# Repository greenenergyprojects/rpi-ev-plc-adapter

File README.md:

# rpi-ev-plc-adapter

Electrovehicle CP/PLC Adapter for Raspberry PI

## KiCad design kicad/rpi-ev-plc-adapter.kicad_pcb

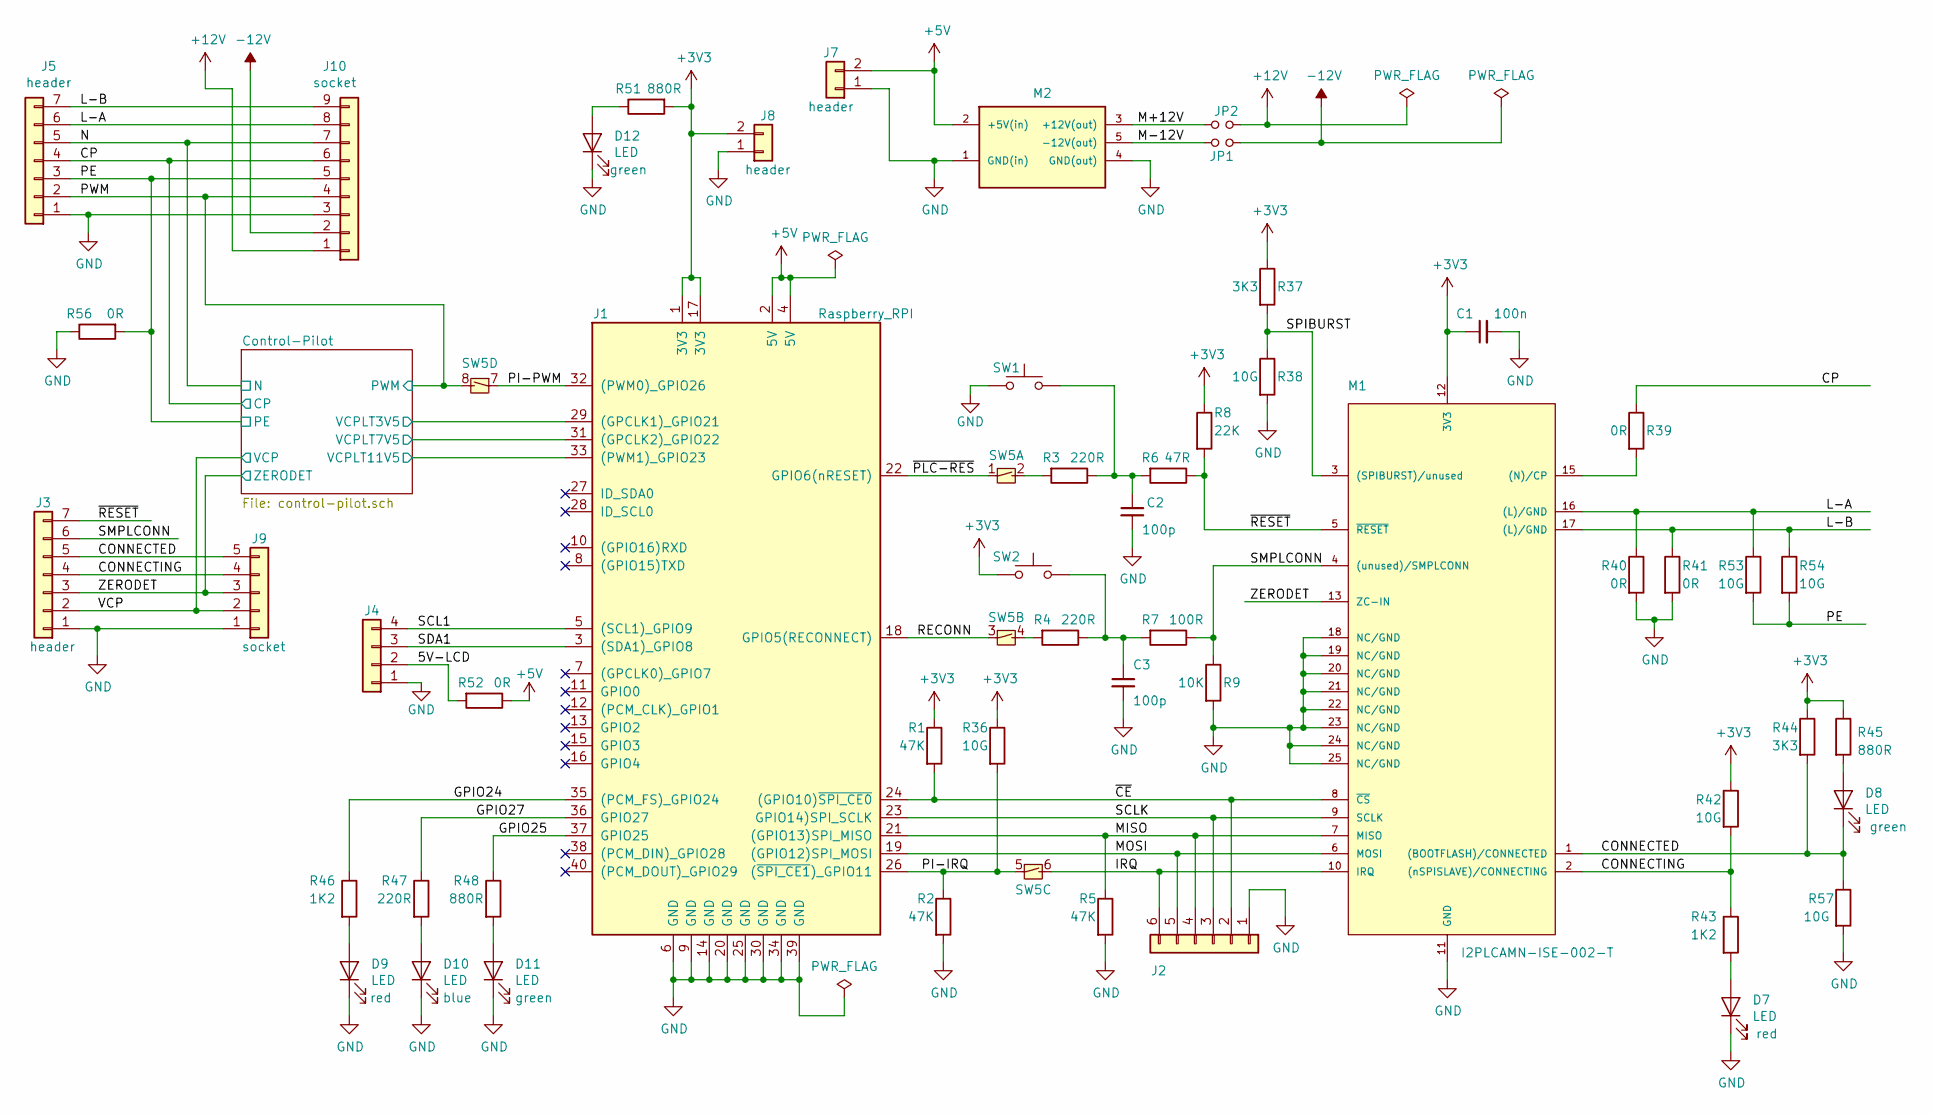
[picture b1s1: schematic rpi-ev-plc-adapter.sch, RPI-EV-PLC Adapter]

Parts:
C1: 100n; c-1206-hand-soldering
C2, C3: 100p; c-1206-hand-soldering
D7, D8, D9, D10, D11, D12: LED; LED_0805_HandSoldering
J1: Raspberry_RPI; Raspberry-PI
J2: Conn_01x06; idc-header-1x06-p2.54mm-vertical
J3, J5: header; idc-header-1x07-p2.54mm-vertical
J4: header; idc-header-1x04-p2.54mm-vertical
J7, J8: header; idc-header-1x02-p2.54mm-vertical
J9: socket; idc-socket-vertical-2.54mm_1x05
J10: socket; idc-socket-1x09-p2.54mm-vertical
JP1, JP2: Jumper_NO_Small; idc-header-1x02-p2.54mm-vertical
M1: I2PLCAMN-ISE-002-T
M2: supply-5VtoPM12V_ebay-253052736386; 5V-to-PM12V_ebay-253052736386
R1, R2, R5: 47K; r-1206-hand-soldering
R3, R4, R47: 220R; r-1206-hand-soldering
R6: 47R; r-1206-hand-soldering
R7: 100R; r-1206-hand-soldering
R8: 22K; r-1206-hand-soldering
R9: 10K; r-1206-hand-soldering
R36, R38, R42, R53, R54, R57: 10G; r-0805-hand-soldering
R37, R44: 3K3; r-1206-hand-soldering
R39, R40, R41, R52, R56: 0R; r-1206-hand-soldering
R43, R46: 1K2; r-1206-hand-soldering
R45, R51: 880R; r-1206-hand-soldering
R48: 880R; r-0805-hand-soldering
SW1, SW2: push-button_ebay-183284526496; push-button-smd-4.5x4.5mm-black
SW5: dip-switch-4x2pos-smd-1.27mm

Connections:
+3V3: C1.1, J1.1 (3V3), J1.17 (3V3), J8.2, M1.12 (3V3), R1.1, R8.1, R36.1, R37.1, R42.1, R44.1, R45.1, R51.2, SW2.1; also elsewhere on the board
+5V: J1.2 (5V), J1.4 (5V), J7.2, M2.2 (+5V(in)), R52.1
+12V: J10.1, JP2.2; also elsewhere on the board
-12V: J10.2, JP1.2; also elsewhere on the board
/5V-LCD: J4.2, R52.2
/CONNECTED: D8.1 (K), J3.5, J9.5, M1.1 ((BOOTFLASH)/CONNECTED), R44.2, R57.1
/CONNECTING: J3.4, J9.4, M1.2 ((nSPISLAVE)/CONNECTING), R42.2, R43.1
/CP: J5.4, J10.6, R39.1; also elsewhere on the board
/Control-Pilot/VCPLT3V5: J1.29 ((GPCLK1)_GPIO21); also elsewhere on the board
/Control-Pilot/VCPLT7V5: J1.31 ((GPCLK2)_GPIO22); also elsewhere on the board
/Control-Pilot/VCPLT11V5: J1.33 ((PWM1)_GPIO23); also elsewhere on the board
/GPIO24: J1.35 ((PCM_FS)_GPIO24), R46.1
/GPIO25: J1.37 (GPIO25), R48.1
/GPIO27: J1.36 (GPIO27), R47.1
/IRQ: J2.6, M1.10 (IRQ), SW5.6 (4)
/L-A: J5.6, J10.8, M1.16 ((L)/GND), R40.1, R53.1
/L-B: J5.7, J10.9, M1.17 ((L)/GND), R41.1, R54.1
/M+12V: JP2.1, M2.3 (+12V(out))
/M-12V: JP1.1, M2.5 (-12V(out))
/MISO: J1.21 ((GPIO13)SPI_MISO), J2.4, M1.7 (MISO), R5.1
/MOSI: J1.19 ((GPIO12)SPI_MOSI), J2.5, M1.6 (MOSI)
/N: J5.5, J10.7; also elsewhere on the board
/PE: J5.3, J10.5, R53.2, R54.2, R56.2; also elsewhere on the board
/PI-IRQ: J1.26 ((~SPI_CE1~)_GPIO11), R2.1, R36.2, SW5.5 (3)
/PI-PWM: J1.32 ((PWM0)_GPIO26), SW5.7 (3)
/PWM: J5.2, J10.4, SW5.8 (4); also elsewhere on the board
/RECONN: J1.18 (GPIO5(RECONNECT)), SW5.3
/SCL1: J1.5 ((SCL1)_GPIO9), J4.4
/SCLK: J1.23 (GPIO14)SPI_SCLK), J2.3, M1.9 (SCLK)
/SDA1: J1.3 ((SDA1)_GPIO8), J4.3
/SMPLCONN: J3.6, M1.4 ((unused)/SMPLCONN), R7.1, R9.1
/SPIBURST: M1.3 ((SPIBURST)/unused), R37.2, R38.1
/VCP: J3.2, J9.2; also elsewhere on the board
/ZERODET: J3.3, J9.3, M1.13 (ZC-IN); also elsewhere on the board
/~CE: J1.24 ((GPIO10)~SPI_CE0~), J2.2, M1.8 (~CS), R1.2
/~PLC-RES: J1.22 (GPIO6(nRESET)), SW5.1
/~RESET: J3.7, M1.5 (~RESET), R6.1, R8.2
GND: C1.2, C2.2, C3.2, D7.1 (K), D9.1 (K), D10.1 (K), D11.1 (K), D12.1 (K), J1.6 (GND), J1.9 (GND), J1.14 (GND), J1.20 (GND), J1.25 (GND), J1.30 (GND), J1.34 (GND), J1.39 (GND), J2.1, J3.1, J4.1, J5.1, J7.1, J8.1, J9.1, J10.3, M1.11 (GND), M1.18 (NC/GND), M1.19 (NC/GND), M1.20 (NC/GND), M1.21 (NC/GND), M1.22 (NC/GND), M1.23 (NC/GND), M1.24 (NC/GND), M1.25 (NC/GND), M2.1 (GND(in)), M2.4 (GND(out)), R2.2, R5.2, R9.2, R38.2, R40.2, R41.2, R56.1, R57.2, SW1.1; also elsewhere on the board
unnamed: C2.1, R3.1, R6.2, SW1.2
unnamed: C3.1, R4.1, R7.2, SW2.2
unnamed: D7.2 (A), R43.2
unnamed: D8.2 (A), R45.2
unnamed: D9.2 (A), R46.2
unnamed: D10.2 (A), R47.2
unnamed: D11.2 (A), R48.2
unnamed: D12.2 (A), R51.1
unnamed: M1.15 ((N)/CP), R39.2
unnamed: R3.2, SW5.2
unnamed: R4.2, SW5.4

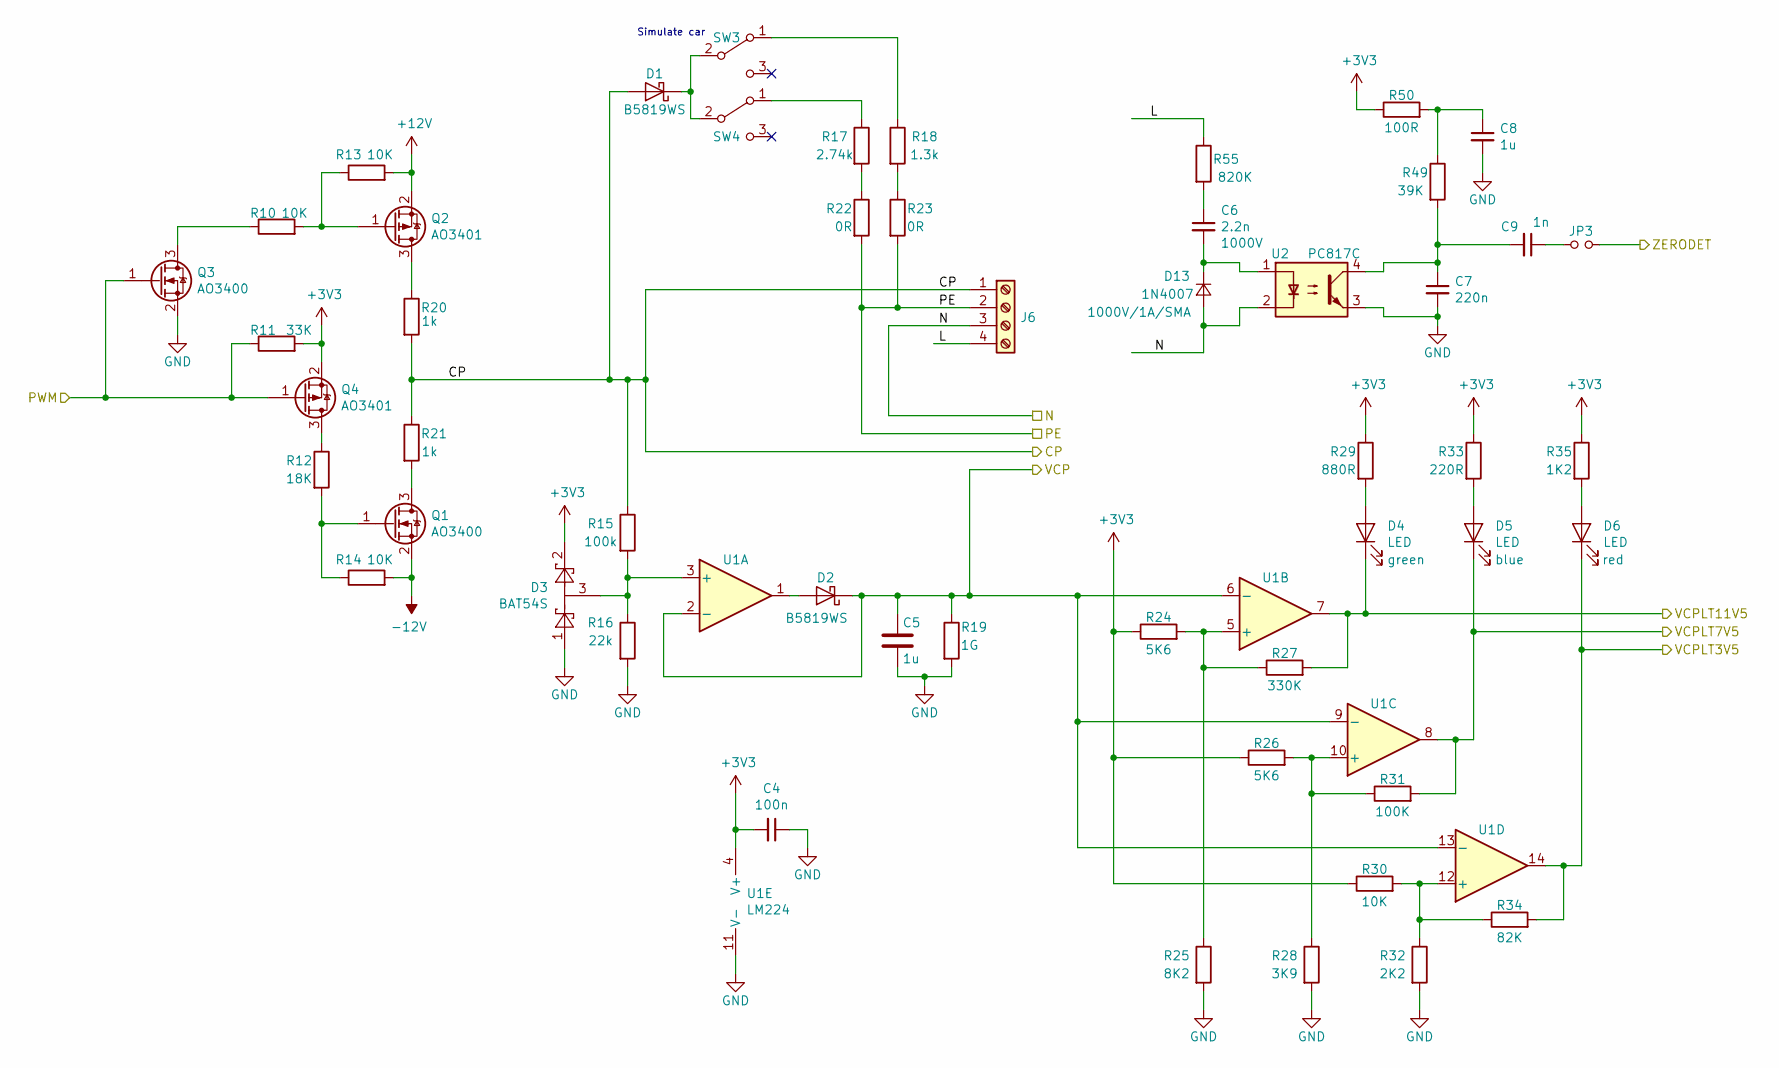
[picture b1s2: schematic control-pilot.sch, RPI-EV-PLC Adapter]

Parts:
C4: 100n; c-1206-hand-soldering
C5, C8: 1u; c-1206-hand-soldering
C6: 2.2n; c-1206-hand-soldering
C7: 220n; c-1206-hand-soldering
C9: 1n; c-1206-hand-soldering
D1, D2: B5819WS; sod-323_hand-soldering
D3: BAT54S; sot-23_hand-soldering
D4, D5, D6: LED; LED_0805_HandSoldering
D13: 1N4007; sma_hand-soldering
J6: Screw_Terminal_01x04; screw-terminal-230v-16a-5mm-4pin
JP3: Jumper_NO_Small; idc-header-1x02-p2.54mm-vertical
Q1, Q3: AO3400; sot-23_hand-soldering
Q2, Q4: AO3401; sot-23_hand-soldering
R10, R13, R14, R30: 10K; r-1206-hand-soldering
R11: 33K; r-1206-hand-soldering
R12: 18K; r-1206-hand-soldering
R15: 100k; r-1206-hand-soldering
R16: 22k; r-1206-hand-soldering
R17: 2.74k; r-1206-hand-soldering
R18: 1.3k; r-1206-hand-soldering
R19: 1G; r-1206-hand-soldering
R20, R21: 1k; r-1206-hand-soldering
R22, R23: 0R; r-1206-hand-soldering
R24, R26: 5K6; r-1206-hand-soldering
R25: 8K2; r-1206-hand-soldering
R27: 330K; r-1206-hand-soldering
R28: 3K9; r-1206-hand-soldering
R29: 880R; r-1206-hand-soldering
R31: 100K; r-1206-hand-soldering
R32: 2K2; r-1206-hand-soldering
R33: 220R; r-1206-hand-soldering
R34: 82K; r-1206-hand-soldering
R35: 1K2; r-1206-hand-soldering
R49: 39K; r-1206-hand-soldering
R50: 100R; r-1206-hand-soldering
R55: 820K; r-1206-hand-soldering
SW3, SW4: SS-12D00G3; switch_ss-12d00g3
U1: LM224; soic-14_hand-soldering
U2: PC817C; sop-4-pc817

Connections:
+3V3: C4.2, D3.2, Q4.2 (S), R11.2, R24.1, R26.1, R29.1, R30.1, R33.1, R35.1, R50.1, U1.4 (V+); also elsewhere on the board
+12V: Q2.2 (S), R13.2; also elsewhere on the board
-12V: Q1.2 (S), R14.2; also elsewhere on the board
/CP: D1.2 (A), J6.1, R15.1, R20.2, R21.1; also elsewhere on the board
/Control-Pilot/L: J6.4, R55.1
/Control-Pilot/VCPLT3V5: D6.1 (K), R34.2, U1.14; also elsewhere on the board
/Control-Pilot/VCPLT7V5: D5.1 (K), R31.2, U1.8; also elsewhere on the board
/Control-Pilot/VCPLT11V5: D4.1 (K), R27.2, U1.7; also elsewhere on the board
/N: D13.2 (A), J6.3, U2.2; also elsewhere on the board
/PE: J6.2, R22.2, R23.2; also elsewhere on the board
/PWM: Q3.1 (G), Q4.1 (G), R11.1; also elsewhere on the board
/VCP: C5.1, D2.1 (K), R19.1, U1.2 (-), U1.6 (-), U1.9 (-), U1.13 (-); also elsewhere on the board
/ZERODET: JP3.2; also elsewhere on the board
GND: C4.1, C5.2, C7.2, C8.2, D3.1, Q3.2 (S), R16.2, R19.2, R25.2, R28.2, R32.2, U1.11 (V-), U2.3; also elsewhere on the board
unnamed: C6.1, R55.2
unnamed: C6.2, D13.1 (K), U2.1
unnamed: C7.1, C9.2, R49.2, U2.4
unnamed: C8.1, R49.1, R50.2
unnamed: C9.1, JP3.1
unnamed: D1.1 (K), SW3.2 (B), SW4.2 (B)
unnamed: D2.2 (A), U1.1
unnamed: D3.3, R15.2, R16.1, U1.3 (+)
unnamed: D4.2 (A), R29.2
unnamed: D5.2 (A), R33.2
unnamed: D6.2 (A), R35.2
unnamed: Q1.1 (G), R12.2, R14.1
unnamed: Q1.3 (D), R21.2
unnamed: Q2.1 (G), R10.2, R13.1
unnamed: Q2.3 (D), R20.1
unnamed: Q3.3 (D), R10.1
unnamed: Q4.3 (D), R12.1
unnamed: R17.1, SW4.1 (A)
unnamed: R17.2, R22.1
unnamed: R18.1, SW3.1 (A)
unnamed: R18.2, R23.1
unnamed: R24.2, R25.1, R27.1, U1.5 (+)
unnamed: R26.2, R28.1, R31.1, U1.10 (+)
unnamed: R30.2, R32.1, R34.1, U1.12 (+)

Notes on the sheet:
Simulate car

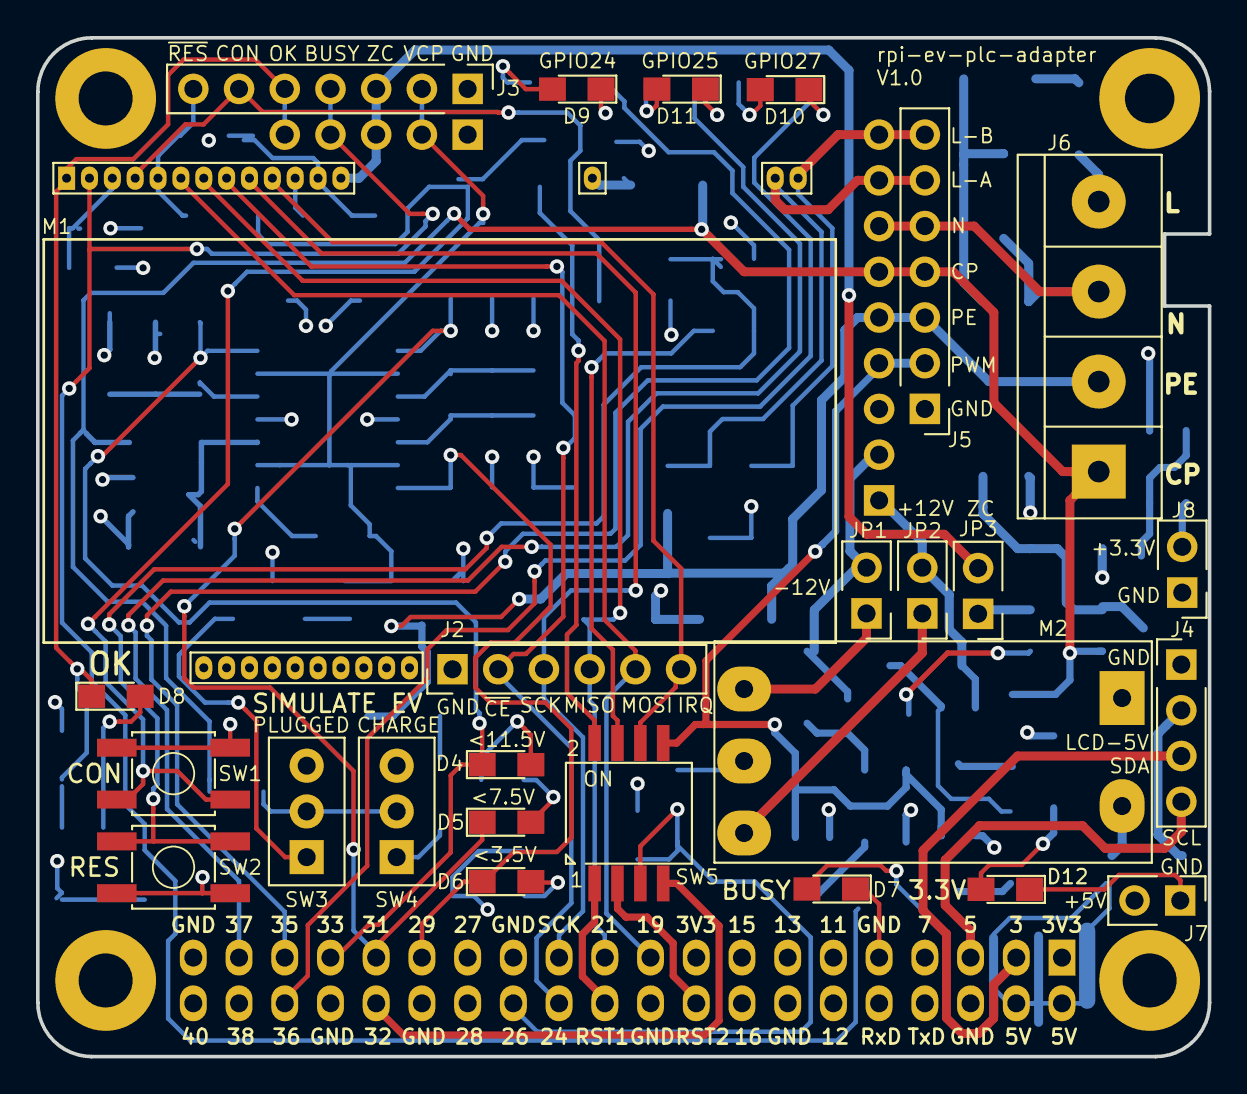
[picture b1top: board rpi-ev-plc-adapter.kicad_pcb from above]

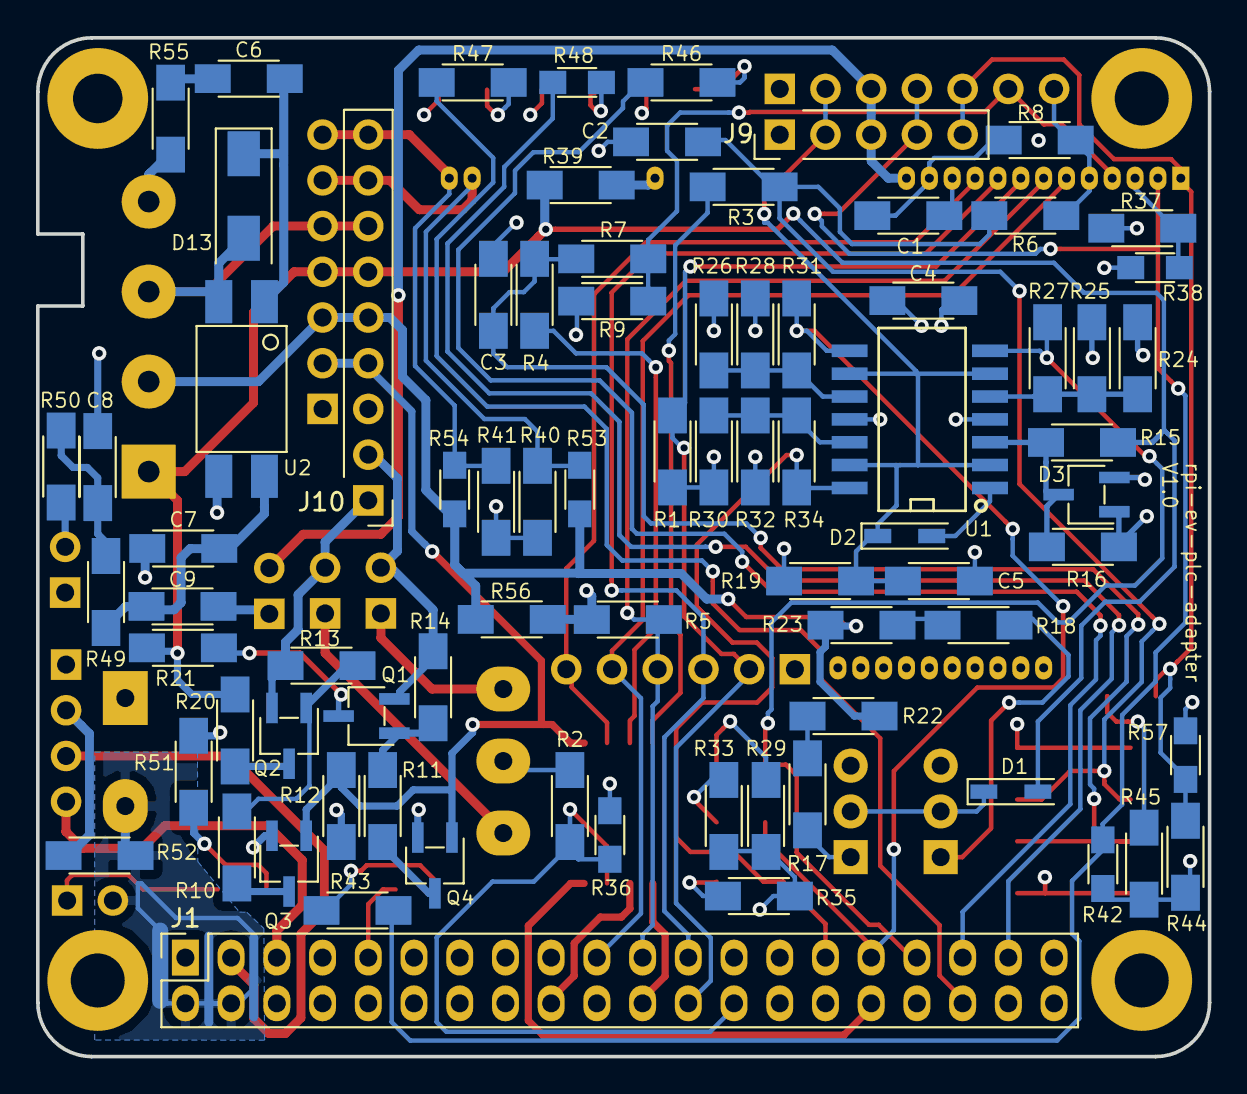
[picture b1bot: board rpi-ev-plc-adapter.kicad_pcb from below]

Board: 4 copper layers, 65.1 x 56.6 mm, 105 parts (78 on the bottom side), 74 nets.

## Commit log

2019-12-31 initial commit, KiCad schematic and placement finished
2020-01-05 routing finished
2020-01-18 removing rescue lib
2020-02-09 pcb fix for modem with 1.27mm connector finished
2020-02-12 schematic/pcb V1.0 finished
2020-02-14 Checks/Fixxes done, V1.0 ready for tape out
2020-02-14 Tapeout V1.0
